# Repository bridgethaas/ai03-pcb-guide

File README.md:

# ai03-pcb-guide

A macropad pcb designed following the ai03 PCB Designer Guide, https://wiki.ai03.com/books/pcb-design/chapter/pcb-designer-guide.

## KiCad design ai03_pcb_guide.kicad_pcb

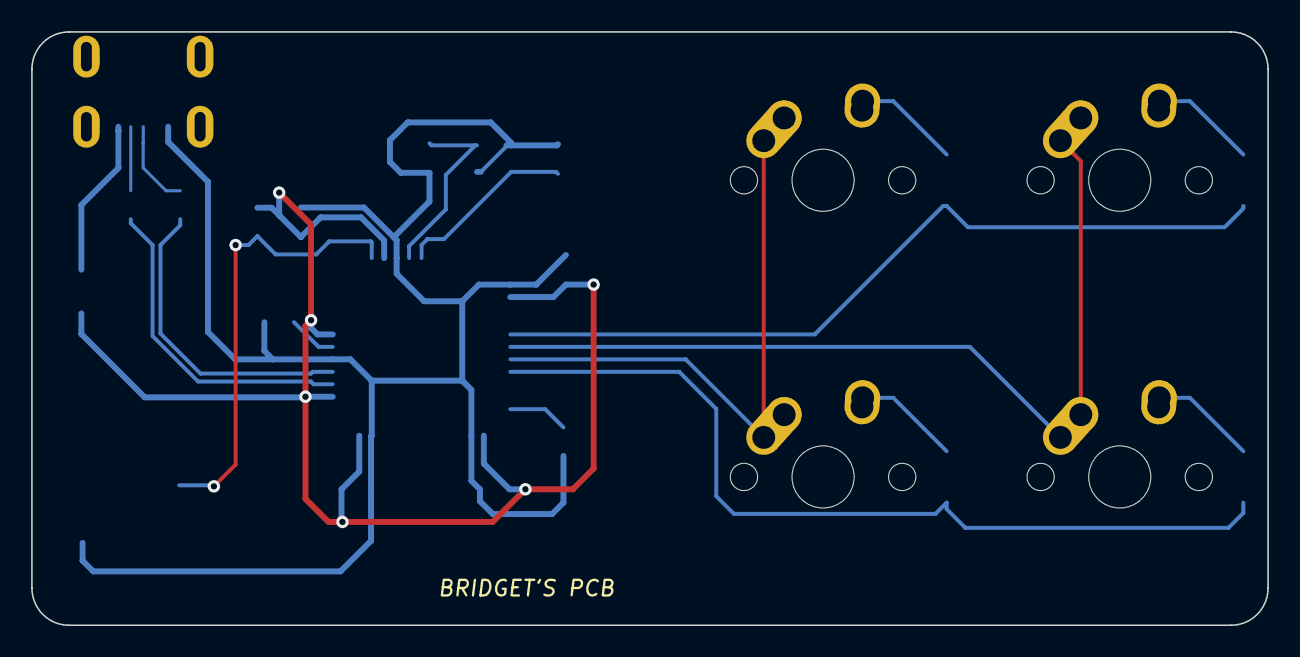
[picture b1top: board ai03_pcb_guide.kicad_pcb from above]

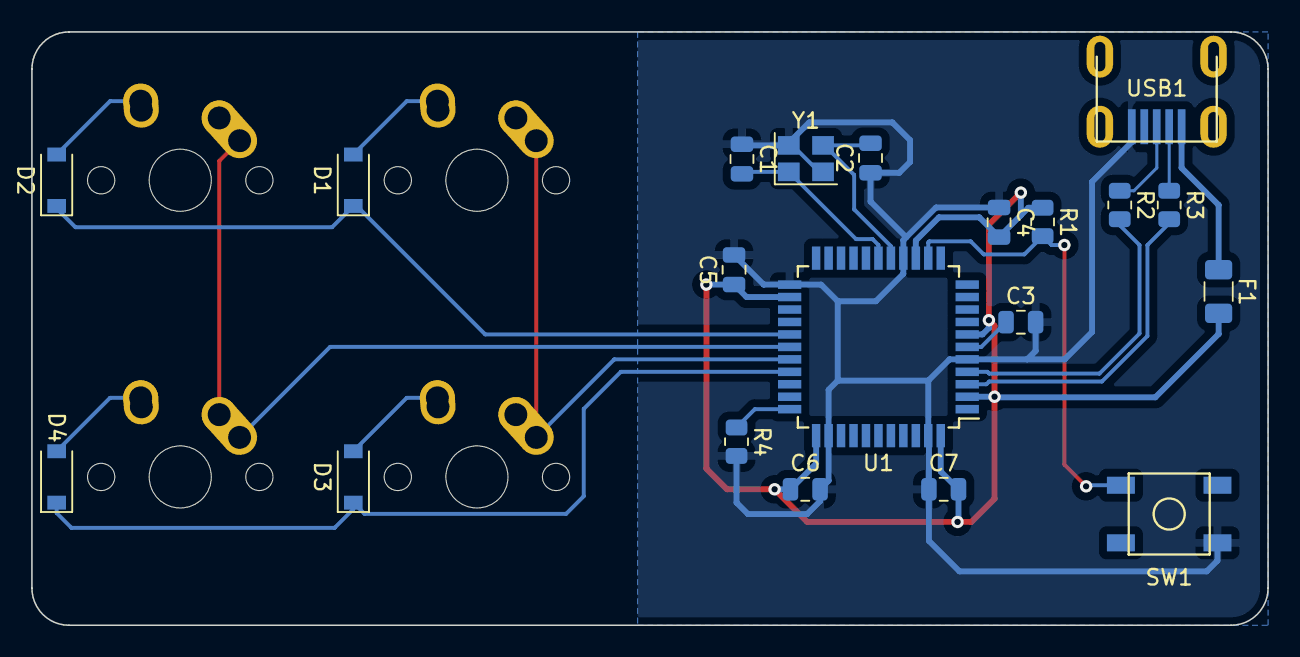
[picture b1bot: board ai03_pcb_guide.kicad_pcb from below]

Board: 2 copper layers, 79.4 x 38.1 mm, 24 parts (20 on the bottom side), 20 nets.

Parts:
C1, C2: 22 pF; C_0805_2012Metric
C3: 1 uF; C_0805_2012Metric
C4, C5, C6: 0.1 uF; C_0805_2012Metric
C7: 10 uF; C_0805_2012Metric
D1, D2, D3, D4: SOD-123; D_SOD-123
F1: 500mA; Fuse_1206_3216Metric
MX1, MX2, MX3, MX4: MX-NoLED; MX-1U-NoLED
R1, R4: 10k; R_0805_2012Metric
R2, R3: 22; R_0805_2012Metric
SW1: SW_Push; SKQG-1155865
U1: ATmega32U4-A; TQFP-44_10x10mm_P0.8mm
USB1: Molex-0548190589
Y1: 16 MHz; Crystal_SMD_3225-4Pin_3.2x2.5mm

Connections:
+5V: C4.2, C5.1, C6.1, C7.2, F1.2, R1.1, U1.2 (UVCC), U1.7 (VBUS), U1.14 (VCC), U1.24 (AVCC), U1.34 (VCC), U1.44 (AVCC)
/COL0: MX1.1 (COL), MX3.1 (COL), U1.29 (PB5)
/COL1: MX2.1 (COL), MX4.1 (COL), U1.28 (PB4)
/D+: R2.1, USB1.3 (D+)
/D-: R3.1, USB1.4 (D-)
/ROW0: D1.1 (K), D2.1 (K), U1.27 (PD7)
/ROW1: D3.1 (K), D4.1 (K), U1.30 (PB6)
GND: C1.1, C2.1, C3.2, C4.1, C5.2, C6.2, C7.1, R4.2, SW1.1, U1.5 (UGND), U1.15 (GND), U1.23 (GND), U1.35 (GND), U1.43 (GND), USB1.1 (GND), Y1.2, Y1.4
unnamed: C1.2, U1.17 (XTAL1), Y1.1
unnamed: C2.2, U1.16 (XTAL2), Y1.3
unnamed: C3.1, U1.6 (UCAP)
unnamed: D1.2 (A), MX1.2 (ROW)
unnamed: D2.2 (A), MX2.2 (ROW)
unnamed: D3.2 (A), MX3.2 (ROW)
unnamed: D4.2 (A), MX4.2 (ROW)
unnamed: R1.2, SW1.2, U1.13 (~RESET)
unnamed: R2.2, U1.4 (D+)
unnamed: R3.2, U1.3 (D-)
unnamed: R4.1, U1.33 (~HWB/PE2)
VCC: F1.1, USB1.5 (VBUS)

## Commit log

2022-01-13 created repository and added readme
2022-01-13 created project files
2022-01-13 add ai03 footprint libraries as submodules
2022-01-13 add libraries into project
2022-01-14 parts 1-3 of the guide
2022-01-14 add gitignore
2022-01-14 assign footprints to components in schematic
2022-01-14 place components
2022-01-14 routing
2022-01-15 end of guide edits
